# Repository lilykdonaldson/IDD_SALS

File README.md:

# Spectrophotometer for Analyzing Liquid Samples (SALS)
Spring 2020, Final Project for ISCI-496 Interactive Device Design (American University)

Lily Donaldson, Éowyn Fain, Cheldina Jean, Fiona Murphey

## Description
This is a device proposal for a spectrophotometer to analyze liquid samples. 

* This device shall analyze a liquid's chemical composition based on its spectral distribution by comparing its spectral data to a pre-defined or user-defined database of liquid spectral readings and returning a 'percent likeness' to these database spectra.
* This device shall allow for the creation of a user-defined database of liquid spectral readings
* This device may also be used to analyze a liquid's turbidity and/or potability.

This device is based off of archived designs from the "Safety Spectrometer" tutuorial formerly hosted by www.creative-technology.net

## File Descriptions
### Bill of Materials (BOM)
1. SALS_BOM.csv
	contents:

	|Part|Value             |Device                 |Package      |Description                               |
	|----|------------------|-----------------------|-------------|------------------------------------------|
	|D1  |BLUE              |LED-BLUE0603           |LED-0603     |Blue SMD LED                              |
	|D2  |Yellow            |LED-YELLOW0603         |LED-0603     |Yellow SMD LED                            |
	|D3  |PINK              |LED-PINK1206           |LED-1206     |Pink SMD LED                              |
	|D4  |RED               |LED-RED0603            |LED-0603     |Red SMD LED                               |
	|D5  |LED-IRSIDE_EMITTER|LED-IRSIDE_EMITTER     |LTE-302      |Infrared LED (IR)                         |
	|LCD1|LCD-16X28X2       |LCD-16X28X2            |LCD-8X2      |Standard text-only 16x2 parallel input LCD|
	|PH1 |PHOTOCELLD11      |PHOTOCELLD11           |D11XX_H      |Photo Sensor                              |
	|R1  |2.2k              |R-US_0204/5            |0204/5       |RESISTOR, American symbol                 |
	|R2  |10k               |R-US_0204/5            |0204/5       |RESISTOR, American symbol                 |
	|R3  |1k                |R-US_0204/5            |0204/5       |RESISTOR, American symbol                 |
	|R4  |1k                |R-US_0204/5            |0204/5       |RESISTOR, American symbol                 |
	|R5  |220               |R-US_0204/5            |0204/5       |RESISTOR, American symbol                 |
	|R6  |220               |R-US_0204/5            |0204/5       |RESISTOR, American symbol                 |
	|R7  |220               |R-US_0204/5            |0204/5       |RESISTOR, American symbol                 |
	|R8  |220               |R-US_0204/5            |0204/5       |RESISTOR, American symbol                 |
	|R9  |220               |R-US_0204/5            |0204/5       |RESISTOR, American symbol                 |
	|SW1 |                  |SWITCH_PUSHBUTTONEVQ-PE|TACT_PANA-EVQ|Buttons                                   |
	|SW2 |                  |SWITCH_PUSHBUTTONEVQ-PE|TACT_PANA-EVQ|Buttons                                   |
	|U$1 |TEENSY_4.0        |TEENSY_4.0             |TEENSY_4.0   |                                          |

### CAD Files for Case
1. SALS_Case.f3d

### Skeleton Code
1. spectrophotometer_skeleton_code.ino

> /* This code is an archive of http://www.creative-technology.net/MAKE/Spectrometer_Code.pdf 
> from April 15, 2010. The original file can be accessed on the WayBack Machine (https://web.archive.org/) */

### Circuit Board
#### Schematic
1. SALS.sch
2. SALS_schematic.pdf

#### PCB Design
3. SALS.sch
4. SALS_BRD.pdf

### Work Breakdown Structure (WBS)

### Class Presentations
1a. Prototype A.pdf

1b. Prototype A_SALS WBS Step 1.0_Device Proposal.pdf

2. Prototype B.pdf

## Further Development
Because of our university moving online due to the ongoing COVID-19 situation, we were not able fabricate this device. 
This documentation may be used to continue the project.
Future steps may include:
* Further case design and 3D printing
* Development and testing of skeleton code 
* Database development (sample liquids)
* Holistic device testing and liquid sampling

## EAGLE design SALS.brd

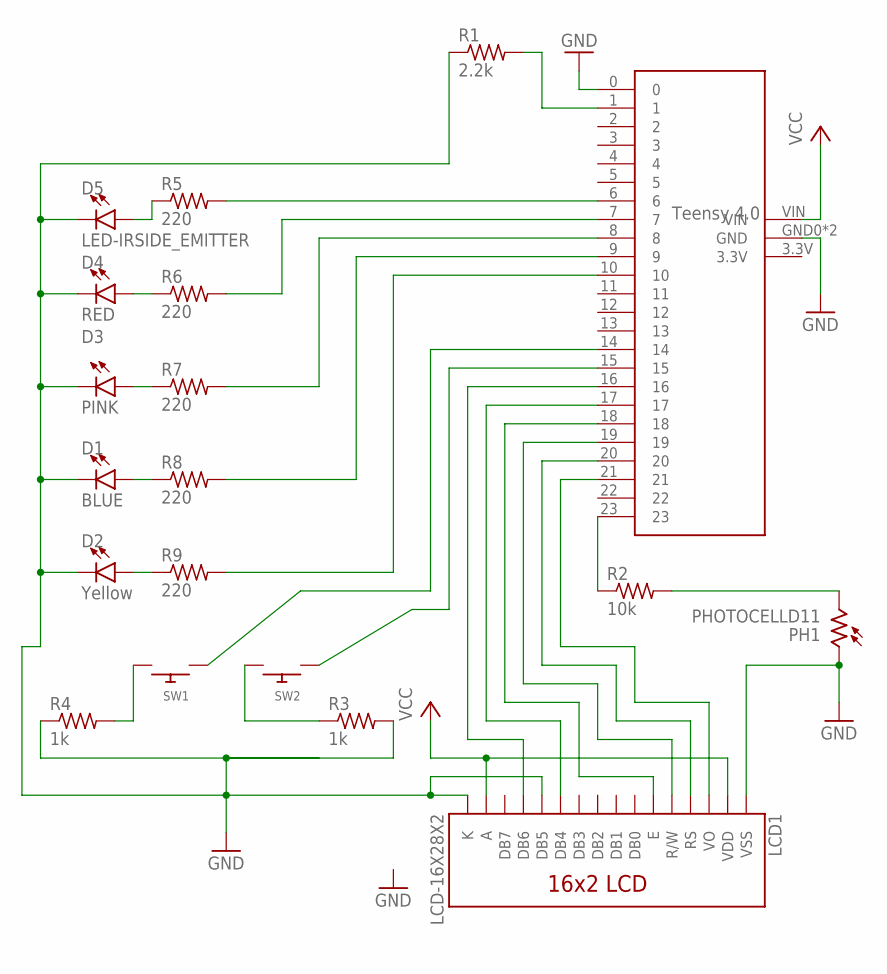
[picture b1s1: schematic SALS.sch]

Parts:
D1: BLUE; LED-0603
D2: Yellow; LED-0603
D3: PINK; LED-1206
D4: RED; LED-0603
D5: LED-IRSIDE_EMITTER; LTE-302
LCD1: LCD-16X28X2; LCD-8X2
PH1: PHOTOCELLD11; D11XX_H
R1: 2.2k; 0204/5
R2: 10k; 0204/5
R3, R4: 1k; 0204/5
R5, R6, R7, R8, R9: 220; 0204/5
SW1, SW2: SWITCH_PUSHBUTTONEVQ-PE; TACT_PANA-EVQ
U$1: TEENSY_4.0

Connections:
GND: D1.C, D2.C, D3.C, D4.C, D5.C, LCD1.1 (VSS), LCD1.12 (DB5), LCD1.16 (K), PH1.1, R1.1, R3.2, R4.1, U$1.0, U$1.GND0 (GND), U$1.GND1 (GND)
unnamed: D5.A, R5.1
unnamed: D4.A, R6.1
unnamed: D3.A, R7.1
unnamed: D1.A, R8.1
unnamed: D2.A, R9.1
unnamed: PH1.2, R2.2
unnamed: LCD1.11 (DB4), U$1.17
unnamed: R1.2, U$1.1
unnamed: R4.2, SW1.P$2
unnamed: R3.1, SW2.P$2
unnamed: LCD1.13 (DB6), U$1.16
unnamed: R2.1, U$1.23
unnamed: R5.2, U$1.6
unnamed: R6.2, U$1.7
unnamed: R7.2, U$1.8
unnamed: R8.2, U$1.9
unnamed: R9.2, U$1.10
unnamed: SW1.P$1, U$1.14
unnamed: SW2.P$1, U$1.15
unnamed: LCD1.5 (R/W), U$1.19
unnamed: LCD1.6 (E), U$1.18
unnamed: LCD1.4 (RS), U$1.20
unnamed: LCD1.3 (VO), U$1.21
VCC: LCD1.2 (VDD), LCD1.15 (A), U$1.VIN

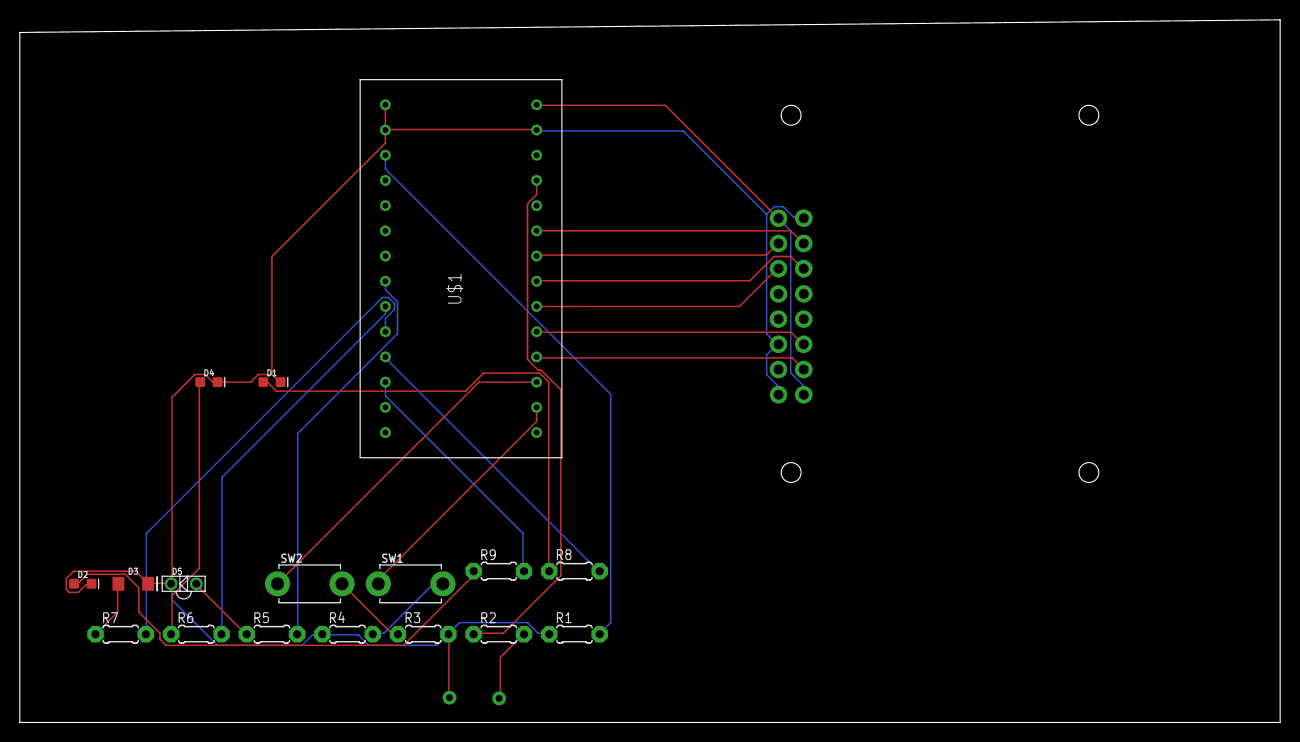
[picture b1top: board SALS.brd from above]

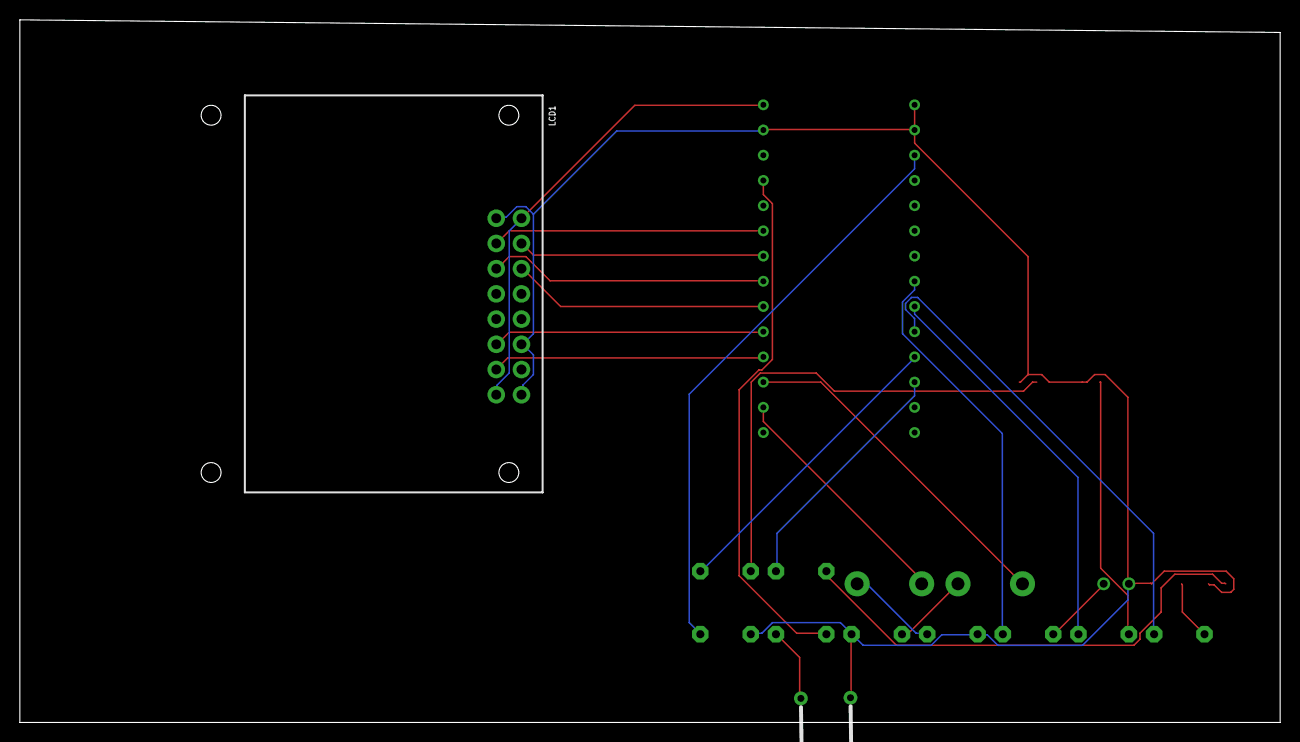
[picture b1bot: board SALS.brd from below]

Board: 2 copper layers, 127.0 x 70.8 mm, 19 parts (2 on the bottom side), 25 nets.

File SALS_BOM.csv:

"Part";"Value";"Device";"Package";"Description";"";
"D1";"BLUE";"LED-BLUE0603";"LED-0603";"Blue SMD LED";"";
"D2";"Yellow";"LED-YELLOW0603";"LED-0603";"Yellow SMD LED";"";
"D3";"PINK";"LED-PINK1206";"LED-1206";"Pink SMD LED";"";
"D4";"RED";"LED-RED0603";"LED-0603";"Red SMD LED";"";
"D5";"LED-IRSIDE_EMITTER";"LED-IRSIDE_EMITTER";"LTE-302";"Infrared LED (IR)";"";
"LCD1";"LCD-16X28X2";"LCD-16X28X2";"LCD-8X2";"Standard text-only 16x2 parallel input LCD";"";
"PH1";"PHOTOCELLD11";"PHOTOCELLD11";"D11XX_H";"Photo Sensor";"";
"R1";"2.2k";"R-US_0204/5";"0204/5";"RESISTOR, American symbol";"";
"R2";"10k";"R-US_0204/5";"0204/5";"RESISTOR, American symbol";"";
"R3";"1k";"R-US_0204/5";"0204/5";"RESISTOR, American symbol";"";
"R4";"1k";"R-US_0204/5";"0204/5";"RESISTOR, American symbol";"";
"R5";"220";"R-US_0204/5";"0204/5";"RESISTOR, American symbol";"";
"R6";"220";"R-US_0204/5";"0204/5";"RESISTOR, American symbol";"";
"R7";"220";"R-US_0204/5";"0204/5";"RESISTOR, American symbol";"";
"R8";"220";"R-US_0204/5";"0204/5";"RESISTOR, American symbol";"";
"R9";"220";"R-US_0204/5";"0204/5";"RESISTOR, American symbol";"";
"SW1";"";"SWITCH_PUSHBUTTONEVQ-PE";"TACT_PANA-EVQ";"Buttons";"";
"SW2";"";"SWITCH_PUSHBUTTONEVQ-PE";"TACT_PANA-EVQ";"Buttons";"";
"U$1";"TEENSY_4.0";"TEENSY_4.0";"TEENSY_4.0";"";"";

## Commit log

2020-04-30 file dump
2020-04-30 more file dump
2020-04-30 add skeleton code
2020-04-30 more more files
2020-04-30 CAD Case
2020-04-30 mispelling fix
2020-04-30 more pcb
2020-04-30 rename WOB
2020-04-30 Case1 Edit name
2020-04-30 WBS markdown friendly
2020-04-30 wbs not wob...

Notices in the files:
parts and their libraries:
SparkFun-LED: Licensing: Creative Commons ShareAlike 4.0 International - https://creativecommons.org/licenses/by-sa/4.0
